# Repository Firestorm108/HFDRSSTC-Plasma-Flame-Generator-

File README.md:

# HFDRSSTC-Plasma-Flame-Generator-
A plasma flame generator, or high frequency dual resonant solid state tesla coil! It uses some really clever electronics to achieve this, and is a staple in plasma physics, being able to produce 4" flames at less than 500W of power. It runs off mains 120VAC, and is based of the IRFP460 power MOSFET. Inspired and derived from the works of Styropyro, Steve Ward, Plasma Channel, and Elecrow. 

# Bill of Materials (BOM)

| Item | Price | Link |
|------|------:|------|
| Screw Terminals | $2 | https://www.aliexpress.us/item/3256806456550715.html |
| Rectifiers | $2 | https://www.aliexpress.us/item/3256807891203177.htm |
| 1W Transformer | $10 | https://www.aliexpress.us/item/2255800847488657.html |
| 35V 4700uF Electrolytics | $5 | https://www.aliexpress.us/item/3256801889213205.html |
| LM7812 Voltage Regulator | $3 | https://www.aliexpress.us/item/3256806033968605.html |
| 16V 330uF Electrolytics | $4 | https://www.aliexpress.us/item/3256801889213205.html |
| 250V 330uF Electrolytics | $5 | https://www.aliexpress.us/item/3256801890525893.html |
| 10uH Inductors | $5 | https://www.aliexpress.us/item/3256806693688205.html |
| IRFP460 MOSFETs | $3 | https://www.aliexpress.us/item/3256806648557481.html |
| TO-247 Heatsink | $1 | https://www.aliexpress.us/item/3256805656895845.html |
| PVC Coupler *(Out of Pocket)* | $5 | https://www.amazon.com/dp/B0DP5XQ1QM |
| 1kV 0.1uF Film Capacitors | $3 | https://www.aliexpress.us/item/3256808548022383.html |
| 10K Potentiometers | $3 | https://www.aliexpress.us/item/3256809269867205.html |
| 28AWG Magnet Wire *(Out of Pocket)* | $12 | https://www.amazon.com/dp/B07DYF53ZN |
| 18AWG Primary Wire | $3 | https://www.aliexpress.us/item/2251832439120214.html |
| Perfboard | $3 | https://www.aliexpress.us/item/3256806802956681.html |

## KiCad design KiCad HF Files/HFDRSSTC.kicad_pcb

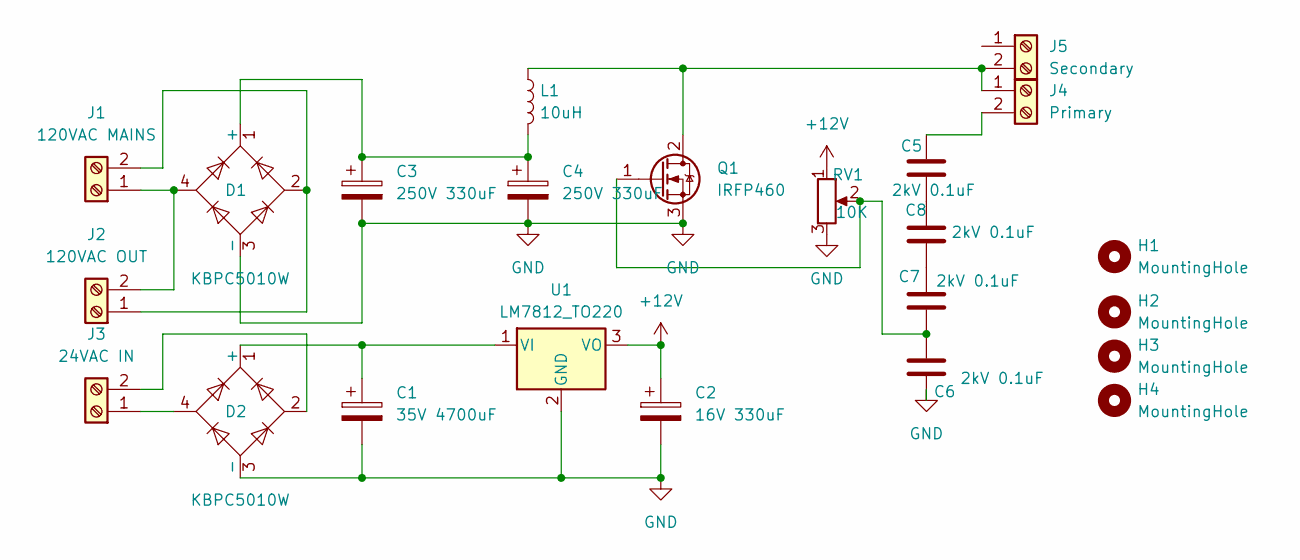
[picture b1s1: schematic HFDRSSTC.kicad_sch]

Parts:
C1: 35V 4700uF; C_Radial_D18.0mm_H35.5mm_P7.50mm
C2: 16V 330uF; C_Radial_D10.0mm_H16.0mm_P5.00mm
C3, C4: 250V 330uF; C_Radial_D18.0mm_H35.5mm_P7.50mm
C5, C6, C7, C8: 2kV 0.1uF; C_Rect_L7.2mm_W2.5mm_P5.00mm_FKS2_FKP2_MKS2_MKP2
D1, D2: KBPC5010W; Diode_Bridge_GeneSiC_KBPC_W
H1, H2, H3, H4: MountingHole; MountingHole_3.2mm_M3
J1: 120VAC MAINS; TE_282837-2
J2: 120VAC OUT; TE_282837-2
J3: 24VAC IN; TE_282837-2
J4: Primary; TE_282837-2
J5: Secondary; TE_282837-2
L1: 10uH; L_Toroid_Horizontal_D16.8mm_P14.70mm_Vishay_TJ3_BigPads
Q1: IRFP460; TO-247-3_Vertical
RV1: 10K; Potentiometer_TT_P0915N
U1: LM7812_TO220; TO-220-3_Vertical

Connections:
+12V: C2.1, RV1.1, U1.3 (VO)
GND: C1.2, C2.2, C3.2, C4.2, C6.2, D1.3 (-), D2.3 (-), Q1.3 (S), RV1.3, U1.2 (GND)
unnamed: C5.2, C8.1
unnamed: C7.1, C8.2
unnamed: C3.1, C4.1, D1.1 (+), L1.2
unnamed: C1.1, D2.1 (+), U1.1 (VI)
unnamed: D1.4, J1.1, J2.2
unnamed: D1.2, J1.2, J2.1
unnamed: D2.4, J3.1
unnamed: D2.2, J3.2
unnamed: J4.1, J5.2, L1.1, Q1.2 (D)
unnamed: C5.1, J4.2
unnamed: C6.1, C7.2, Q1.1 (G), RV1.2

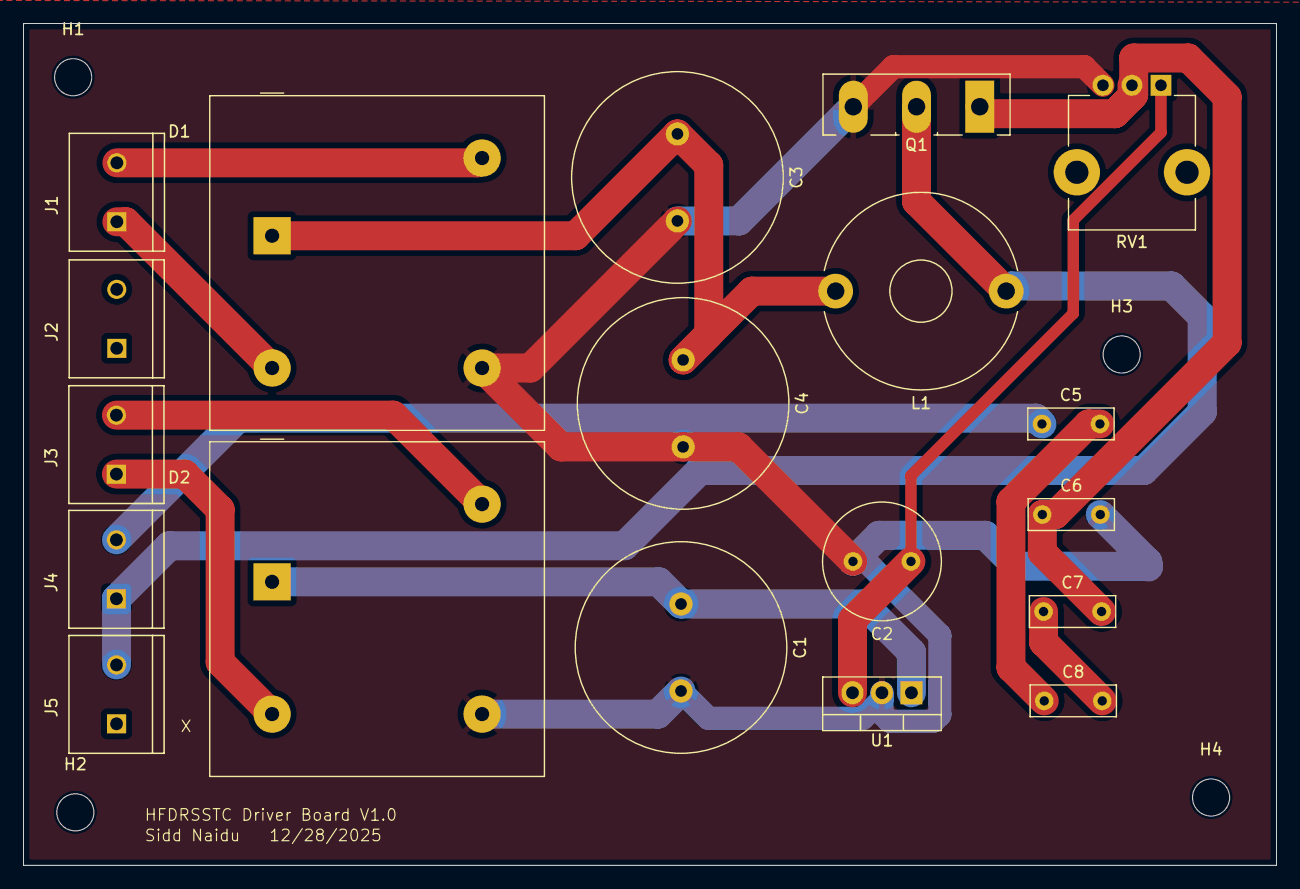
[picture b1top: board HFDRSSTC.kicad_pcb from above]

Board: 2 copper layers, 108.0 x 72.6 mm, 23 parts (0 on the bottom side), 13 nets.

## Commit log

2026-01-06 Revise component list with updated prices and links
    Updated item prices and links in the README.
2026-01-06 Revise BOM format in README.md
    Updated the Bill of Materials (BOM) section to use a table format.
